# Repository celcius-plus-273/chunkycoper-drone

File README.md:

# chunkycoper-drone

Repository to host all of the design files regarding my quadcopter drone project.

The repository is broken down into three main sections:
1. Electronic Design Files (boards)
2. Code & Firmware (control)
3. Mechanical Design Files (shell)

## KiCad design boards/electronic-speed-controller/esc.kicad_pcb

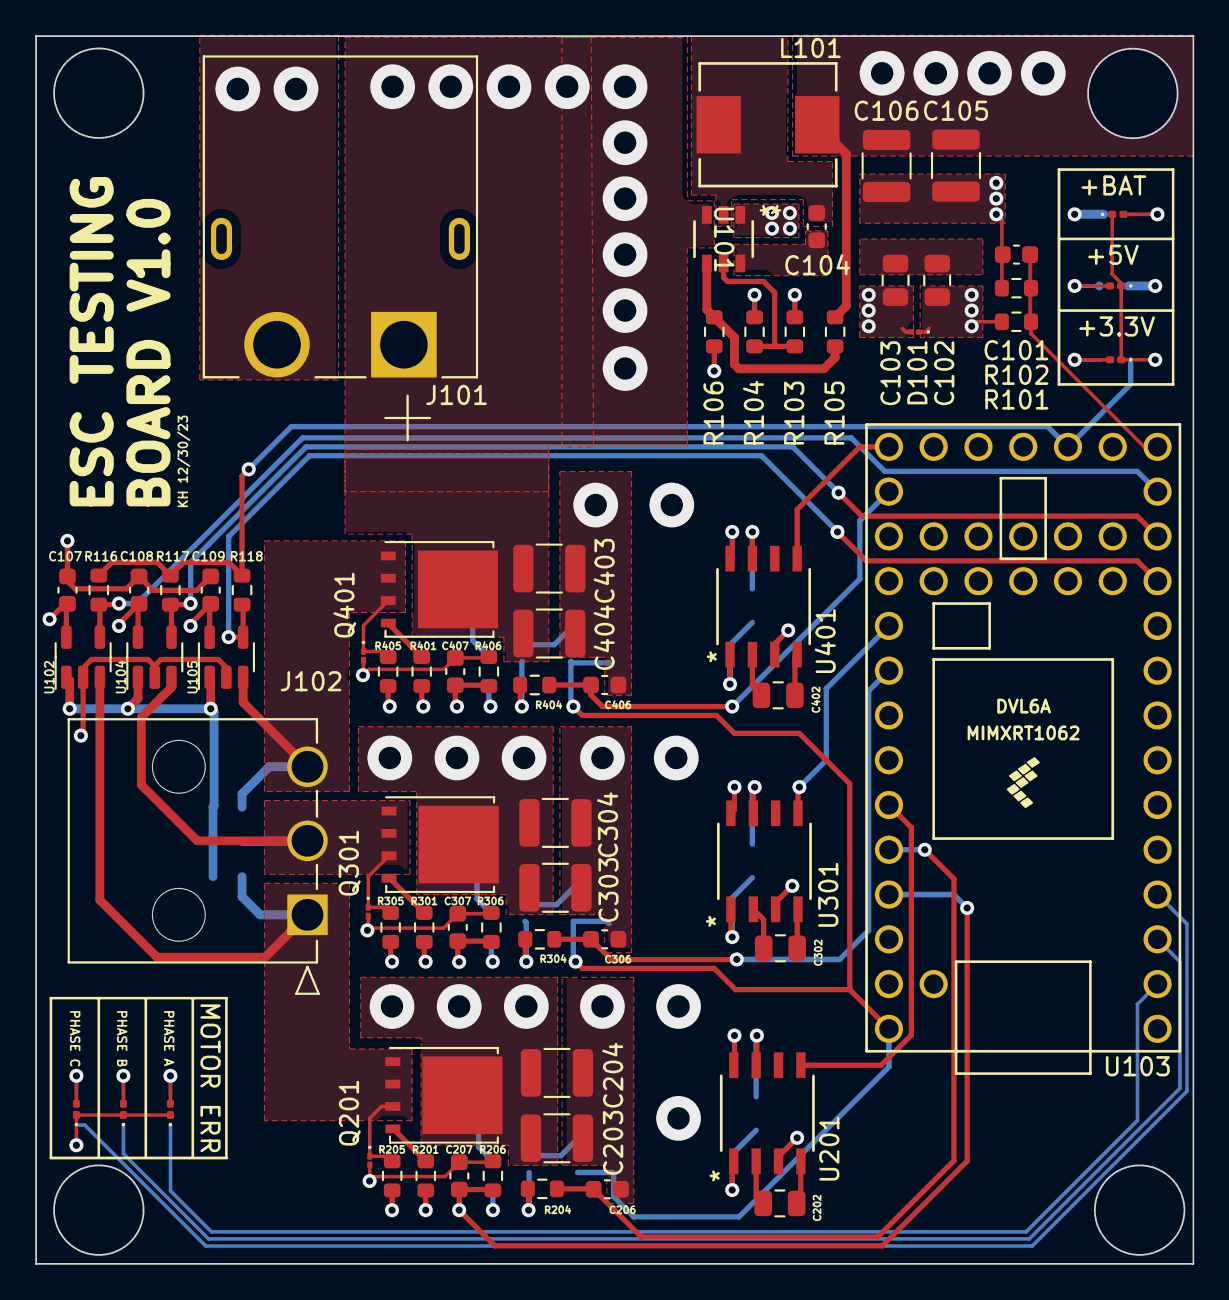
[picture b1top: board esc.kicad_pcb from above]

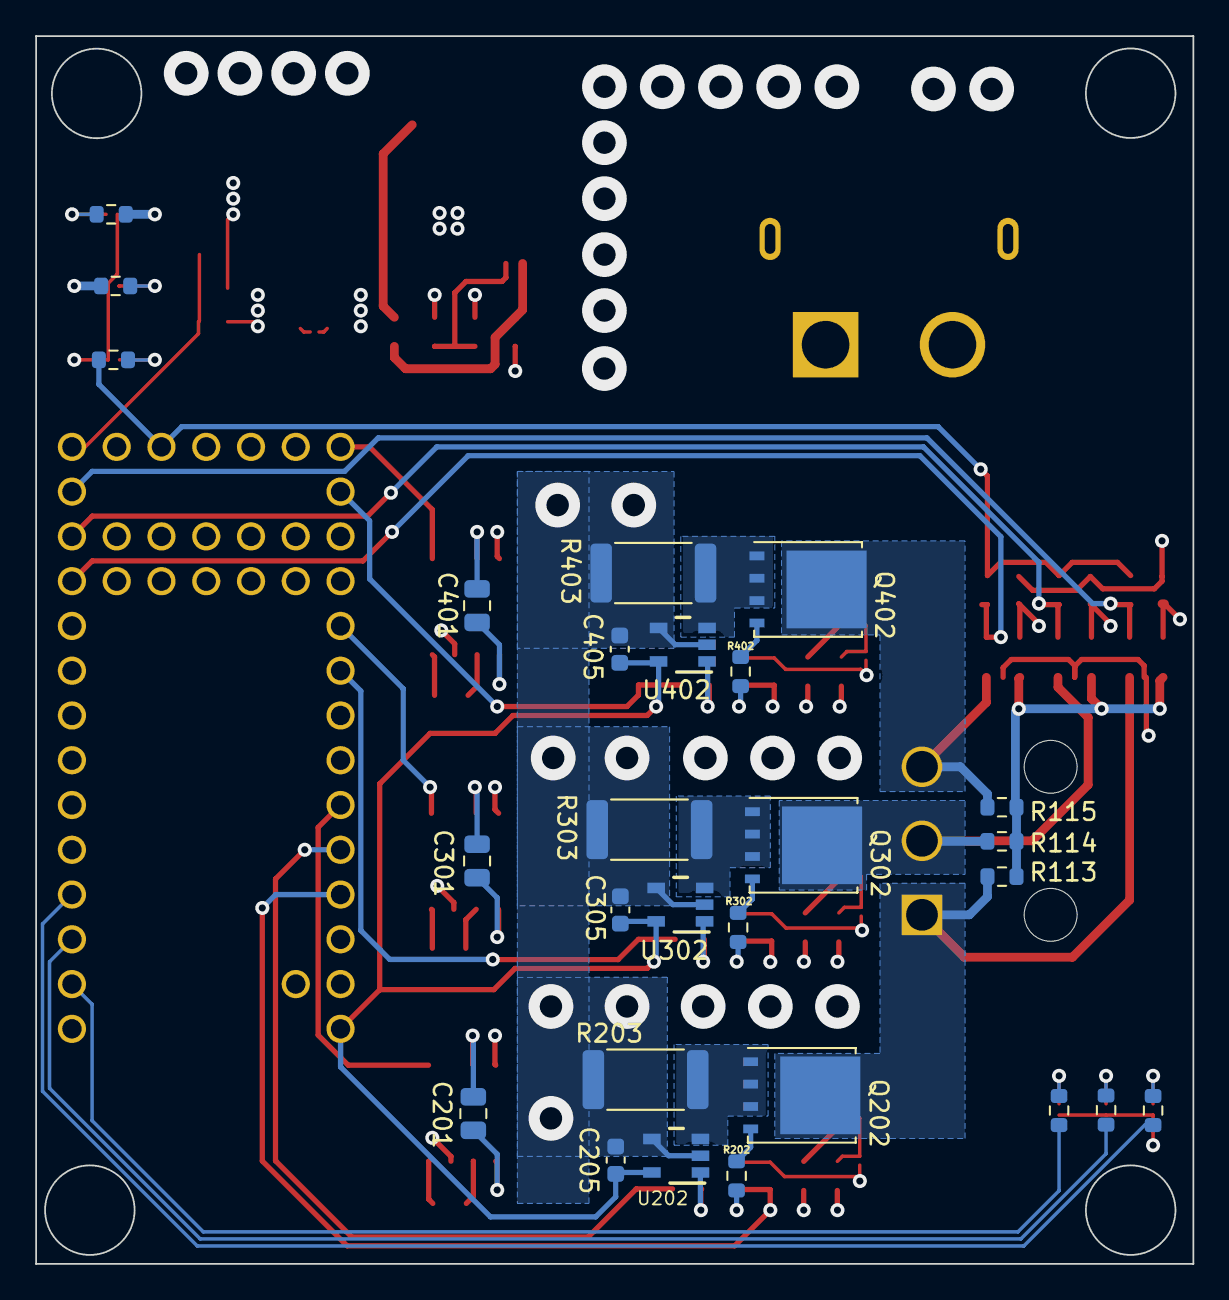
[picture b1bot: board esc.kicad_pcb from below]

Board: 4 copper layers, 65.7 x 69.7 mm, 96 parts (27 on the bottom side), 59 nets.

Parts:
C101, C207, C307, C407: 10nF; C_0603_1608Metric
C102, C103: 4.7uF; C_0805_2012Metric
C104, C107, C108, C109, C205, C305, C405: 0.1uF; C_0603_1608Metric
C105, C106, C203, C204, C303, C304, C403, C404: 22uF; C_1210_3225Metric
C201, C202, C301, C302, C401, C402: 1uF; C_0805_2012Metric
C206, C306, C406: 1nF; C_0603_1608Metric
D101, D201, D301, D401: TVS_0402; D_01005_0402Metric
D102, D103, D104, D105, D106, D107: LED; LED_0201_0603Metric
J101: XT60PW-M; AMASS_XT60PW-M
J102: 39303037; CON_39303037
L101: 10uH; IND_SRP6540-2R2M_BRN
Q201, Q202, Q301, Q302, Q401, Q402: BSC340N08NS3G; TDSON-8-1
R101, R205, R305, R405: 4.7k; R_0603_1608Metric
R102, R107, R204, R206, R304, R306, R404, R406: 1k; R_0603_1608Metric
R103: 110k; R_0603_1608Metric
R104: 11.3k; R_0603_1608Metric
R105: 100K; R_0603_1608Metric
R106: 13.7K; R_0603_1608Metric
R108, R109, R110, R111, R112, R116, R117, R118, R201, R202, R301, R302, R401, R402: 100; R_0603_1608Metric
R113, R114, R115: 10k; R_0603_1608Metric
R203, R303, R403: 2m; R_2512_6332Metric
U101: LMR51420XDDCR; SOT23_DDC_TEX
U102, U104, U105: TL331; SOT-23-5
U103: Teensy4.0; Teensy40
U201, U301, U401: MIC4605-2YM-TR; SOIC-8_M_MCH
U202, U302, U402: INA180A3IDBVR; DBV0005A_N

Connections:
+3.3V: R109.1, R116.1, R117.1, R118.1, U103.16 (3V3), U103.31 (3V3)
+5V: C105.1, C106.1, C205.2, C305.2, C405.2, L101.1, R105.1, R108.1, U103.33 (VIN), U202.5 (VS), U302.5 (VS), U402.5 (VS)
GND: C101.1, C103.2, C105.2, C106.2, C107.2, C108.2, C109.2, C201.2, C203.2, C204.2, C205.1, C206.1, C207.1, C301.2, C303.2, C304.2, C305.1, C306.1, C307.1, C401.2, C403.2, C404.2, C405.1, C406.1, C407.1, D101.2 (A), D102.1 (K), D103.1 (K), D104.1 (K), D105.1 (K), D106.1 (K), D107.1 (K), D201.2 (A), D301.2 (A), D401.2 (A), J101.2 (-), R102.2, R104.2, R106.2, R203.2, R206.2, R303.2, R306.2, R403.2, R406.2, U101.1 (GND), U102.2 (V-), U103.1 (GND), U103.17 (GND), U103.32 (GND), U104.2 (V-), U105.2 (V-), U201.7 (VSS), U202.2 (GND), U202.4 (IN-), U301.7 (VSS), U302.2 (GND), U302.4 (IN-), U401.7 (VSS), U402.2 (GND), U402.4 (IN-)
I_ERROR_A: R110.1, U103.2 (0_RX1_CRX2_CS1)
I_ERROR_B: R111.1, U103.3 (1_TX1_CTX2_MISO1)
I_ERROR_C: R112.1, U103.4 (2_OUT2)
I_SENSE_A: C206.2, R204.2, U103.29 (22_A8_CTX1)
I_SENSE_B: C306.2, R304.2, U103.25 (18_A4_SDA0)
I_SENSE_C: C406.2, R404.2, U103.21 (14_A0_TX3_SPDIF_OUT)
unnamed: C102.2, C103.1
unnamed: D102.2 (A), R107.2
unnamed: D103.2 (A), R108.2
unnamed: D104.2 (A), R109.2
unnamed: D105.2 (A), R110.2
unnamed: D106.2 (A), R111.2
unnamed: D107.2 (A), R112.2
unnamed: Q201.4 (G), R201.2
unnamed: Q202.4 (G), R202.2
unnamed: Q301.4 (G), R301.2
unnamed: Q302.4 (G), R302.2
unnamed: Q401.4 (G), R401.2
unnamed: Q402.4 (G), R402.2
unnamed: C104.2, U101.6 (CB)
unnamed: R103.2, R104.1, U101.5 (EN)
unnamed: R105.2, R106.1, U101.4 (FB)
unnamed: C104.1, L101.2, U101.2 (SW)
unnamed: C202.1, U201.2 (HB)
unnamed: R201.1, U201.3 (HO)
unnamed: C202.2, U201.4 (HS)
unnamed: R202.1, U201.8 (LO)
unnamed: Q202.1 (S), Q202.2 (S), Q202.3 (S), R203.1, U202.3 (IN+)
unnamed: R204.1, U202.1 (OUT)
unnamed: C302.1, U301.2 (HB)
unnamed: R301.1, U301.3 (HO)
unnamed: C302.2, U301.4 (HS)
unnamed: R302.1, U301.8 (LO)
unnamed: Q302.1 (S), Q302.2 (S), Q302.3 (S), R303.1, U302.3 (IN+)
unnamed: R304.1, U302.1 (OUT)
unnamed: C402.1, U401.2 (HB)
unnamed: R401.1, U401.3 (HO)
unnamed: C402.2, U401.4 (HS)
unnamed: R402.1, U401.8 (LO)
unnamed: Q402.1 (S), Q402.2 (S), Q402.3 (S), R403.1, U402.3 (IN+)
unnamed: R404.1, U402.1 (OUT)
PHASE_A: D201.1 (K), J102.1, Q201.1 (S), Q201.2 (S), Q201.3 (S), Q202.5 (D), R113.1, R205.1, U102.3 (+)
PHASE_B: D301.1 (K), J102.2, Q301.1 (S), Q301.2 (S), Q301.3 (S), Q302.5 (D), R114.1, R305.1, U104.3 (+)
PHASE_C: D401.1 (K), J102.3, Q401.1 (S), Q401.2 (S), Q401.3 (S), Q402.5 (D), R115.1, R405.1, U105.3 (+)
PWM_A: U103.28 (21_A7_RX5_BCLK1), U201.5 (PWM)
PWM_B: U103.24 (17_A3_TX4_SDA1), U301.5 (PWM)
PWM_C: U103.20 (13_SCK_CRX1_LED), U401.5 (PWM)
VCC: C102.1, C107.1, C108.1, C109.1, C201.1, C203.1, C204.1, C301.1, C303.1, C304.1, C401.1, C403.1, C404.1, D101.1 (K), J101.1 (+), Q201.5 (D), Q301.5 (D), Q401.5 (D), R101.1, R103.1, R107.1, U101.3 (VIN), U102.5 (V+), U104.5 (V+), U105.5 (V+), U201.1 (VDD), U301.1 (VDD), U401.1 (VDD)
VCC_SENSE: C101.2, R101.2, R102.1, U103.14 (12_MISO_MQSL)
V_NEUTRAL: R113.2, R114.2, R115.2, U102.1 (-), U104.1 (-), U105.1 (-)
V_SENSE_A: C207.2, R205.2, R206.1, U103.30 (23_A9_CRX1_MCLK1)
V_SENSE_B: C307.2, R305.2, R306.1, U103.26 (19_A5_SCL0)
V_SENSE_C: C407.2, R405.2, R406.1, U103.22 (15_A1_RX3_SPDIF_IN)
ZERO_A: R116.2, U102.4, U103.13 (11_MOSI_CTX1)
ZERO_B: R117.2, U103.12 (10_CS_MQSR), U104.4
ZERO_C: R118.2, U103.11 (9_OUT1C), U105.4

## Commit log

2023-06-24 added eagle design files
2023-06-24 added upython files and imu driver
2023-06-25 reorganized repo files
2023-06-25 testing if deleting works
2023-06-25 deleted duplicated files
2023-06-25 Create README.md for control directory
2023-06-25 Create README.md for pcb directory
2023-06-25 added stl 3d design files
2023-12-16 added esc kicad project
2023-12-16 updated readme a little bit
2023-12-16 renamed the directories
2023-12-16 updated readme oreder
2023-12-30 updated MOSFETs
2023-12-30 finished layout and schematic
2023-12-31 simplified PHASE A circuit
2024-01-01 started simplified esc
2024-01-02 added MIC4606 and IRFR mosfet
2024-01-03 changed TVS diode
2024-01-03 finished esc simple schematic
2024-01-09 modified git ignore
